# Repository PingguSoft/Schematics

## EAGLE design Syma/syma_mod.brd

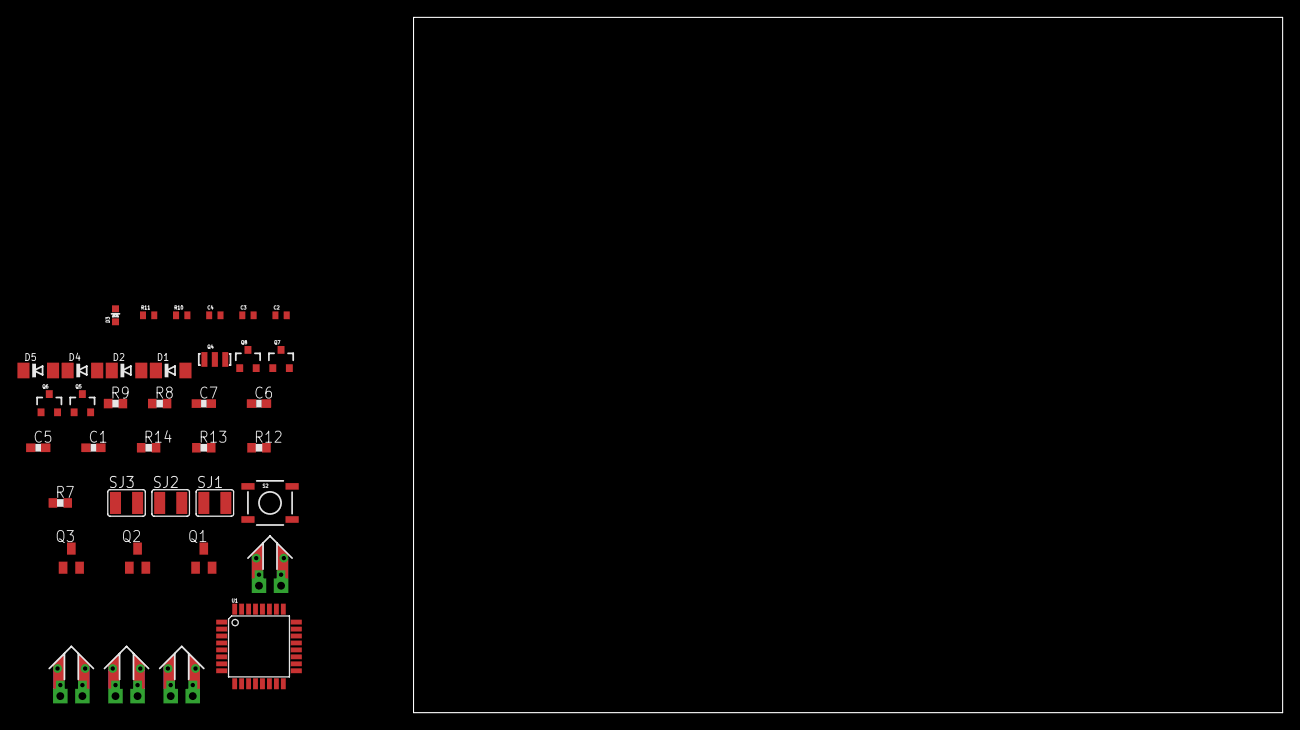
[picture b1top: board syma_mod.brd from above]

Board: 2 copper layers, 100.0 x 80.0 mm, 37 parts (0 on the bottom side), 25 nets, no tracks yet.

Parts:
C1, C5, C6, C7: 470p; C0603
C2, C3, C4: 0.1uF; C0402
D1, D2, D4, D5: MINIMELF
D3: Green; LED-0603
M1, M2, M3, M4: MOTORARM-CORNER; MOTOR-CORNER-2
Q1, Q2, Q3: BSS84; SOT23
Q4: #MHz; RESONATOR-SMD
Q5, Q6, Q7, Q8: DMN2075U; SOT23-3
R7, R12, R13, R14: 680K; R0603
R8: 10K; R0603
R9: 20K; R0603
R10: 10K; C0402
R11: 330; C0402
S2: Reset; TACTILE_SWITCH_SMD
SJ1, SJ2, SJ3: SJW
U1: ATMEGA168#; TQFP32-08

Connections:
AREF: C2.2, U1.20
D3: C1.1, R7.2, U1.1
D9: C7.1, R14.2, U1.13
D10: C5.1, R12.2, U1.14
GND: C2.1, C3.1, D3.C, Q4.2, Q5.2, Q6.2, Q7.2, Q8.2, R7.1, R9.1, R12.1, R13.1, R14.1, S2.1, S2.2, U1.3, U1.5, U1.21
MOSI: C6.1, R13.2, U1.15
unnamed: Q2.3, SJ2.1
unnamed: Q3.3, SJ3.1
unnamed: Q1.3, SJ1.1
unnamed: D3.A, R11.2
unnamed: Q4.1, U1.8
unnamed: Q4.3, U1.7
unnamed: D2.A, M1.B@1, Q6.3
unnamed: C5.2, Q6.1
unnamed: D4.A, M2.B@1, Q7.3
unnamed: C6.2, Q7.1
unnamed: D5.A, M3.B@1, Q8.3
unnamed: C7.2, Q8.1
unnamed: D1.A, M4.B@1, Q5.3
unnamed: C1.2, Q5.1
RESET: C4.1, R10.1, S2.3, S2.4, U1.29
SCK: R11.1, U1.17
SYMA_CAM_TRIG: R8.1, R9.2
VBATT: D1.C, D2.C, D4.C, D5.C, M1.A@1, M2.A@1, M3.A@1, M4.A@1
VCC: C3.2, Q1.2, Q2.2, Q3.2, R10.2, U1.4, U1.6, U1.18

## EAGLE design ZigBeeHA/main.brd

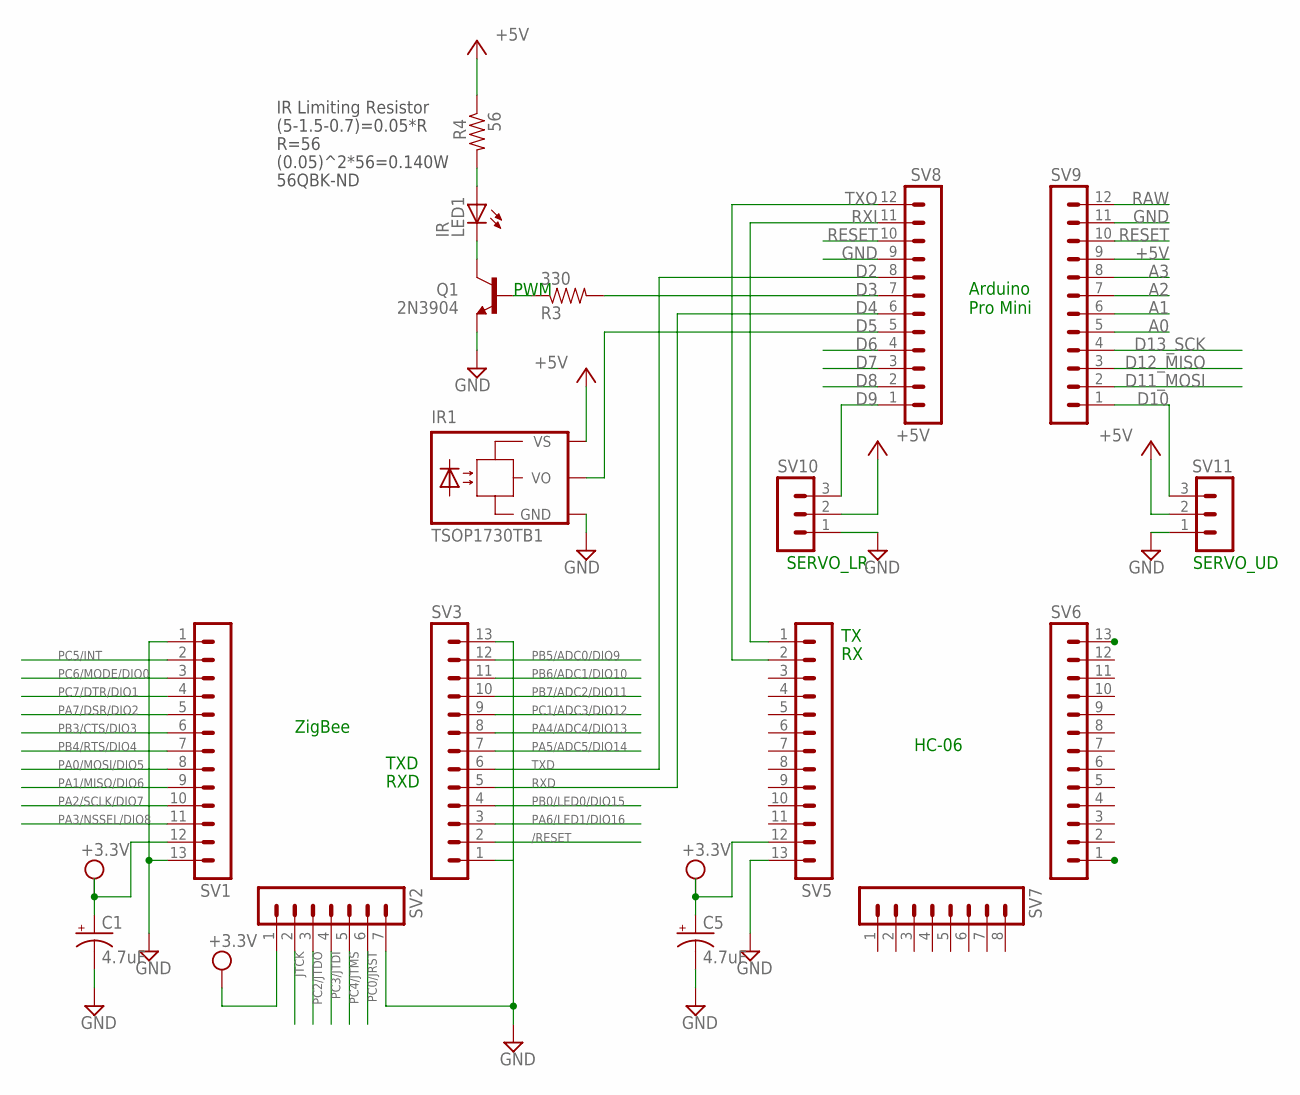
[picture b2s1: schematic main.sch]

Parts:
C1, C5: 4.7uF; SANYO-OSCON_SMD_A5
IR1: TSOP1730TB1; TSOP17_TB1
LED1: IR; LED5MM
Q1: 2N3904; TO-92
R3: 330; AXIAL-0.3
R4: 56; AXIAL-0.3
SV1, SV3, SV5, SV6: MA13-1
SV2: MA07-1
SV7: MA08-1
SV8, SV9: MA12-1
SV10, SV11: MA03-1

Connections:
+5V: IR1.VS, R4.P$1 (1), SV9.9, SV10.2, SV11.2
/RESET: SV3.2
A0: SV9.5
A1: SV9.6
A2: SV9.7
A3: SV9.8
D2: SV8.8
D3: R3.P$2 (2), SV8.7
D4: SV8.6
D5: IR1.VO, SV8.5
D6: SV8.4
D7: SV8.3
D8: SV8.2
D9: SV8.1, SV10.3
D10: SV9.1, SV11.3
D11_MOSI: SV9.2
D12_MISO: SV9.3
D13_SCK: SV9.4
GND: C1.-, C5.-, IR1.GND, Q1.1 (E), SV1.1, SV1.13, SV2.7, SV3.1, SV3.13, SV5.13, SV8.9, SV9.11, SV10.1, SV11.1
GND1: SV6.1, SV6.13
JTCK: SV2.2
unnamed: Q1.2 (B), R3.P$1 (1)
unnamed: LED1.A, R4.P$2 (2)
unnamed: LED1.K (C), Q1.3 (C)
PA0/MOSI/DIO5: SV1.8
PA1/MISO/DIO6: SV1.9
PA2/SCLK/DIO7: SV1.10
PA3/NSSEL/DIO8: SV1.11
PA4/ADC4/DIO13: SV3.8
PA5/ADC5/DIO14: SV3.7
PA6/LED1/DIO16: SV3.3
PA7/DSR/DIO2: SV1.5
PB0/LED0/DIO15: SV3.4
PB3/CTS/DIO3: SV1.6
PB4/RTS/DIO4: SV1.7
PB5/ADC0/DIO9: SV3.12
PB6/ADC1/DIO10: SV3.11
PB7/ADC2/DIO11: SV3.10
PC0/JRST: SV2.6
PC1/ADC3/DIO12: SV3.9
PC2/JTDO: SV2.3
PC3/JTDI: SV2.4
PC4/JTMS: SV2.5
PC5/INT: SV1.2
PC6/MODE/DIO0: SV1.3
PC7/DTR/DIO1: SV1.4
RAW: SV9.12
RESET: SV8.10, SV9.10
RXD: SV3.5
RXI: SV5.1, SV8.11
TXD: SV3.6
TXO: SV5.2, SV8.12
VCC: C1.+, C5.+, SV1.12, SV2.1, SV5.12

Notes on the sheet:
HC-06
ZigBee
Arduino Pro Mini
SERVO_LR
SERVO_UD
(5-1.5-0.7)=0.05*R
R=56
(0.05)^2*56=0.140W
IR Limiting Resistor
56QBK-ND
RXD
TXD
PWM

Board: 2 copper layers, 17 parts (0 on the bottom side), 14 nets, no tracks yet.

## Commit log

2014-03-31 Initial ZigBeeHA
    Initial ZigBeeHA
2014-04-01 parts updated
    parts updated
2014-04-03 1st completion
    1st completion
2014-11-24 Acryl cutting added
2014-11-24 PowerPoint update
2014-11-25 LightSwitchBox fixed
2014-11-25 LightSwitchBox modified
2014-11-26 LightSwitchBox re-fixed
2014-11-27 Arduino is added for Servo control
2014-11-30 RPi version updated
2014-12-19 Acryl design updated
2014-12-19 syma update
2014-12-22 Depth is updated
2014-12-22 source path changed
2014-12-24 outlet box updated
2014-12-30 syma schematic updated
    avr is added
2014-12-31 syma schematic - add voltage sense
2015-03-09 Universal TX - Devention added
2015-03-09 syma update
    eeprom test for bit chip lcd
2015-03-09 update devention
2015-03-10 Codes for universal TX
2015-03-11 Syma X5 is working with universal TX
2015-03-11 test throttle
2015-03-12 YD717 protocol added
2015-03-12 Change address randomization
2015-03-12 data base added
2015-03-13 Serial Protocol added
2015-03-13 Syma X5C test done
    Serial data handling
2015-03-16 Syma X5C camera test done
2015-03-17 -- Folder name changed to Deviation --
    micro USB male connector added to schematic
2015-03-17 V2x2 protocol added
    getProtoOpt is changed to getProtocolOpt
2015-03-18 CFlie and HiSky protocols added
2015-03-18 Add auto code generation to excel sheet
2015-03-18 Syma Protocol test done
2015-03-18 free ram check command added
2015-03-19 Devo protocol added
    Schematic is modified for 4-wire SPI for A7105
2015-03-20 Change time unit to micro second
2015-03-21 Time unit fix
2015-03-30 Add auto baud rate change
2015-03-31 Schematic updated and auto baud rate bug fix
2015-04-01 A7105 related protocols added
2015-04-02 Cleanup codes and RF Power settings added
2015-04-03 Fix Syma flag
2015-04-09 Codes are branched to UniConTX
